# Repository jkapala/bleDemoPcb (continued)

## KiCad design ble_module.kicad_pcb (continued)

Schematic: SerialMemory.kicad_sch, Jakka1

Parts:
C24, C25, C28: 100 nF; C_0603_1608Metric
C26, C27: 22 uF; C_1206_3216Metric
D7, D8, D9: ESD321x; SODFL1608X77N; Manufacturer_Part_Number ESD321DYAR; Mouser Part Number 595-ESD321DYAR
D10: PESD3V3X4UHMYL; SON45P80X130X43-6N; Manufacturer_Part_Number PESD3V3X4UHMYL; Mouser Part Number 771-PESD3V3X4UHMYL
J3: Micro_SD_Card; GCT_MEM2061-01-188-00-A_REVA
R27, R29, R30, R32: 10k; R_0603_1608Metric
R28: 22R; R_0603_1608Metric
R31: 10k; R_0603_1608Metric; not fitted
U4: CAT24C256; SOIC-8_3.9x4.9mm_P1.27mm
U5: MX25L12833FM2I; SOP-8_5.28x5.23mm_P1.27mm

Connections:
+3V3: C24.1, C25.1, C26.1, C27.1, C28.1, D9.1 (K), J3.4 (VDD), R27.1, R29.1, R30.1, R31.2, R32.2, U4.8 (VCC), U5.8 (VCC); also elsewhere on the board
/Serial Memory/DAT1: D7.1 (K), J3.8 (DAT1), R32.1
/Serial Memory/DAT2: D8.1 (K), J3.1 (DAT2), R30.2
EEPROM_WP: U4.7 (WP); also elsewhere on the board
GND: C24.2, C25.2, C26.2, C27.2, C28.2, D7.2 (A), D8.2 (A), D9.2 (A), D10.2 (CA_1), D10.5 (CA_2), J3.6 (VSS), J3.9 (SHIELD), U4.1 (A0), U4.2 (A1), U4.3 (A2), U4.4 (GND), U5.4 (GND); also elsewhere on the board
I2C_SCL: U4.6 (SCL); also elsewhere on the board
I2C_SDA: U4.5 (SDA); also elsewhere on the board
QSPI_CLK: R28.1; also elsewhere on the board
QSPI_CLK_PIN: R28.2, U5.6 (SCLK); also elsewhere on the board
QSPI_IO0: U5.5 (SI/SIO0); also elsewhere on the board
QSPI_IO1: U5.2 (SO/SIO1); also elsewhere on the board
QSPI_IO2: U5.3 (~WP/SIO2); also elsewhere on the board
QSPI_IO3: U5.7 (~HOLD/SIO3); also elsewhere on the board
QSPI_NCS: R27.2, U5.1 (~CS); also elsewhere on the board
SPI2_MISO: D10.1 (K1), J3.7 (DAT0), R31.1; also elsewhere on the board
SPI2_MOSI: D10.4 (K3), J3.3 (CMD); also elsewhere on the board
SPI2_NSS: D10.6 (K4), J3.2 (DAT3/CD), R29.2; also elsewhere on the board
SPI2_SCK: D10.3 (K2), J3.5 (CLK); also elsewhere on the board

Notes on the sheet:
ALT: MX25L12833FZNI-10G
Micro SD
ESD protection
Addr: 1010 000
16 MB NOR Flash
32 KB EEPROM

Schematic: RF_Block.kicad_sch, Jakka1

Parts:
ANT1: AMCA72-2R470G-S1F-T4; AMCA722R470GS1FT4; Manufacturer_Part_Number AMCA72-2R470G-S1F-T4; Mouser Part Number 815-CA722R470GS1FT4
C47, C48: 0.8 pF; C_0402_1005Metric
C49: 0.3 pF; C_0402_1005Metric
J6: Conn_Coaxial; U.FL_Molex_MCRF_73412-0110_Vertical
L3: 2.7 nH; L_0402_1005Metric
L4: L; C_0402_1005Metric; not fitted
L5: 7.3 nH; L_0402_1005Metric
R46: 0R; R_0402_1005Metric; not fitted
U10: DLF162500LT-5028A1; DLF-4_1P6X0P8

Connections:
/RF Block/RF_50_OHM: C49.1, L3.2, U10.1 (IN)
/RF Block/RF_ANTENNA: C47.1, L4.2, R46.1, U10.3 (OUT)
GND: C48.2, C49.2, J6.2 (Ext), L4.1, L5.1, U10.2 (GND), U10.4 (GND); also elsewhere on the board
unnamed: ANT1.1, C47.2, L5.2
unnamed: J6.1 (In), R46.2
RF1: C48.1, L3.1; also elsewhere on the board

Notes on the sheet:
U.FL Connector
2450AT45A0100001E - Johanson, large
AMCA72-2R470G-S1F - Abracon
0402
GJM1555C1HR80WB01D
LQW15AN7N3G00D
LQG15HS2N7S02

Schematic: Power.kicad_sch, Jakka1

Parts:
B1: BAT-HLD-001; BATT_HLDR_LNX
C1, C10: 10 uF; C_0805_2012Metric
C2, C3, C4, C5: 10 nF; C_0603_1608Metric; Voltage 25V
C6, C7: 4.7 uF; C_0805_2012Metric
C8, C9: 330 pF; C_0603_1608Metric
C11, C12: 22 uF; C_1210_3225Metric
C13: 10 uF; C_1210_3225Metric
D1, D2: ESD321x; SODFL1608X77N; Manufacturer_Part_Number ESD321DYAR; Mouser Part Number 595-ESD321DYAR
D3, D4, D5, D6: LED; D_0603_1608Metric
J1: USB_C_Receptacle_USB2.0_16P; GCT_USB4105-GF-A
R1: 0.010R; C_1206_3216Metric
R2, R3: 10k; R_0603_1608Metric
R4, R5, R6, R7: R_US; R_0603_1608Metric
R8, R9, R10, R11: 100k; R_0603_1608Metric
R12, R19: 1k; R_0603_1608Metric
R13, R14, R17, R20: 5.1k; R_0603_1608Metric
R15, R18: 23.2k; R_0603_1608Metric
R16: 0; R_0603_1608Metric
S1: 4-1825059-2; SW_4-1825059-2
TP1: TestPoint; TestPoint_Pad_D1.0mm
U1: TPS25730DREFR; Mouser Part Number 595-TPS25730DREFR
U2: TVS1800DRV; WSON-6-1EP_2x2mm_P0.65mm_EP1x1.6mm

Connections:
3V_RTC: B1.3; also elsewhere on the board
+3V3: R4.1, R5.1, R6.1, R7.1, R16.2; also elsewhere on the board
/Power/ADCIN1: R8.2, S1.15, S1.16, U1.2 (ADCIN1)
/Power/ADCIN1-A: R12.1, S1.2
/Power/ADCIN1-B: R13.1, S1.1
/Power/ADCIN2: R9.2, S1.13, S1.14, U1.3 (ADCIN2)
/Power/ADCIN2-A: R14.1, S1.4
/Power/ADCIN2-B: R15.1, S1.3
/Power/ADCIN3: R10.2, S1.11, S1.12, U1.5 (ADCIN3)
/Power/ADCIN3-A: R17.1, S1.6
/Power/ADCIN3-B: R18.1, S1.5
/Power/ADCIN4: R11.2, S1.9, S1.10, U1.7 (ADCIN4)
/Power/ADCIN4-A: R19.1, S1.8
/Power/ADCIN4-B: R20.1, S1.7
/Power/DBG_ACC: D6.1 (K), U1.10 (DBG_ACC)
/Power/DRAIN: U1.15 (DRAIN_1), U1.30 (DRAIN_2), U1.40 (DRAIN_3)
/Power/PDO_MISMATCH: D4.1 (K), U1.6 (CAP_MIS)
/Power/PLUG_EVENT: D5.1 (K), U1.37 (PLUG_EVENT)
/Power/PLUG_FLIP: D3.1 (K), U1.13 (PLUG_FLIP)
/Power/USB_CC1: C9.1, J1.A5 (CC1), U1.28 (CC1)
/Power/USB_CC2: C8.1, J1.B5 (CC2), U1.29 (CC2)
/Power/VIN_3V3: C10.1, R16.1, U1.38 (VIN_3V3)
/Power/~FAULT_IN: R2.2, U1.18 (~FAULT_IN)
/Power/~SINK_EN: R3.2, U1.19 (~SINK_EN)
GND: B1.2, C1.2, C2.2, C3.2, C4.2, C5.2, C6.2, C7.2, C8.2, C9.2, C10.2, C11.2, C12.2, C13.2, D1.2 (A), D2.2 (A), J1.A1 (GND), J1.A12 (GND), J1.B1 (GND), J1.B12 (GND), J1.S1 (SHIELD), R12.2, R13.2, R14.2, R15.2, R17.2, R18.2, R19.2, R20.2, U1.11 (GND_1), U1.12 (GND_2), U1.14 (GND_3), U1.16 (GND_4), U1.17 (GND_5), U1.26 (RESERVED_1), U1.27 (RESERVED_2), U1.31 (GND_6), U1.34 (GND_7), U1.35 (GND_8), U1.36 (RESERVED_3), U1.39 (GND_9), U1.44 (GND_10), U2.1 (GND), U2.2 (GND), U2.3 (GND), U2.7 (GND); also elsewhere on the board
I2C_SCL: U1.9 (I2CT_SCL); also elsewhere on the board
I2C_SDA: U1.8 (I2CT_SDA); also elsewhere on the board
LDO_3V3: C1.1, R2.1, R3.1, R8.1, R9.1, R10.1, R11.1, U1.1 (LDO_3V3)
unnamed: D3.2 (A), R4.2
unnamed: D4.2 (A), R5.2
unnamed: D5.2 (A), R6.2
unnamed: D6.2 (A), R7.2
unnamed: C7.1, U1.4 (LDO_1V5)
USB_D+: D1.1 (K), J1.A6 (D+), J1.B6 (D+); also elsewhere on the board
USB_D-: D2.1 (K), J1.A7 (D-), J1.B7 (D-); also elsewhere on the board
VBUS_FROM_CONN1: J1.A4 (VBUS), J1.A9 (VBUS), J1.B4 (VBUS), J1.B9 (VBUS), R1.2, TP1.1, U2.4 (IN), U2.5 (IN), U2.6 (IN); also elsewhere on the board
VBUS_FROM_CONN2: C2.1, C3.1, C4.1, C5.1, C6.1, R1.1, U1.23 (VBUS_IN_1), U1.24 (VBUS_IN_2), U1.25 (VBUS_IN_3), U1.32 (VBUS_1), U1.33 (VBUS_2), U1.42 (VBUS_IN_4), U1.43 (VBUS_3); also elsewhere on the board
VBUS_MAIN: C11.1, C12.1, C13.1, U1.20 (PPHV_1), U1.21 (PPHV_2), U1.22 (PPHV_3), U1.41 (PPHV_4); also elsewhere on the board

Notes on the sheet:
USB 2.0 FS conn: USB4105-GF-A
Use TVS2200 for 27.7V clamp and 22V working range
1: Min V 2: Max V 3/4: Sink current
Jumper included to GND to enforce dead battery mode or route power from 3.3V rail
Status LEDs
RTC Battery Holder
Voltage clamped to 22.8V Limiting starting at 18V
LDO_3V3 is an output
10 uF for 3.3V LDO
VBUS ESD
ADDR: 00100 000 or 0010 001
PDO Config Block
leave SBU pins floating
Only USB 2.0 is supported for the STM32WB series.
Do not use

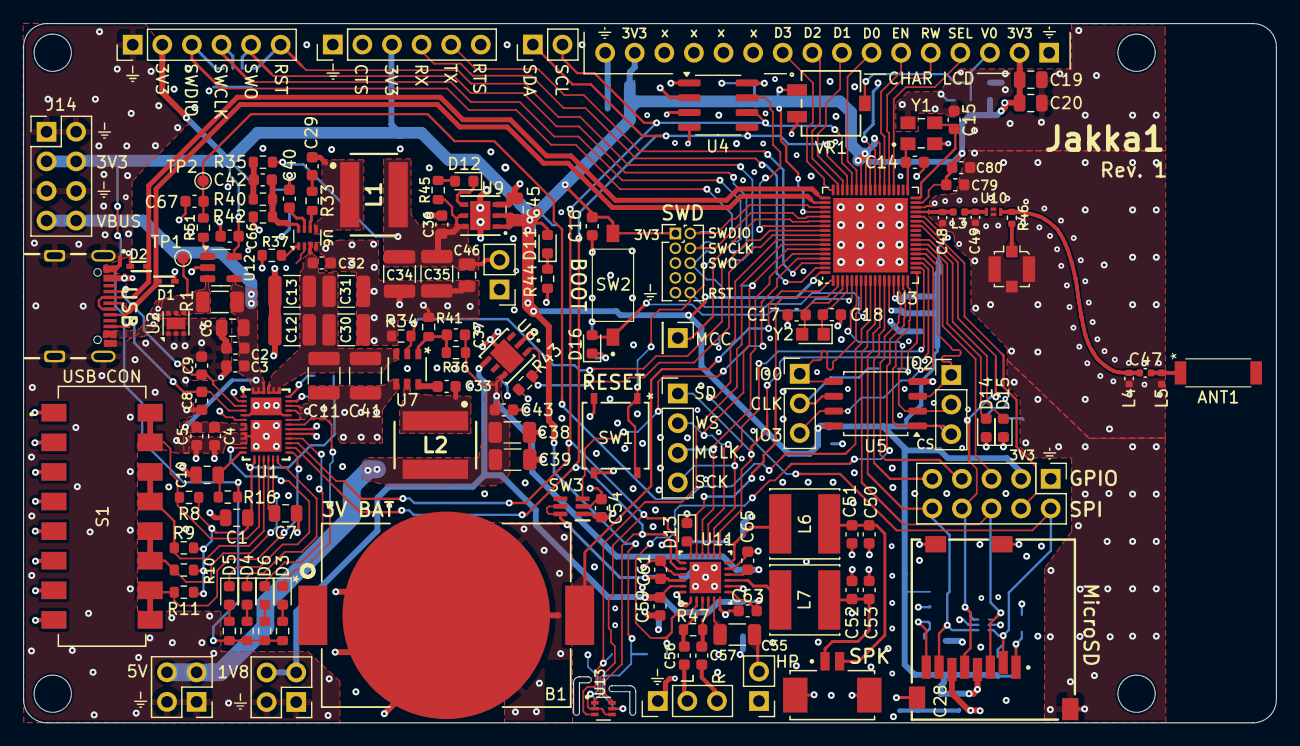
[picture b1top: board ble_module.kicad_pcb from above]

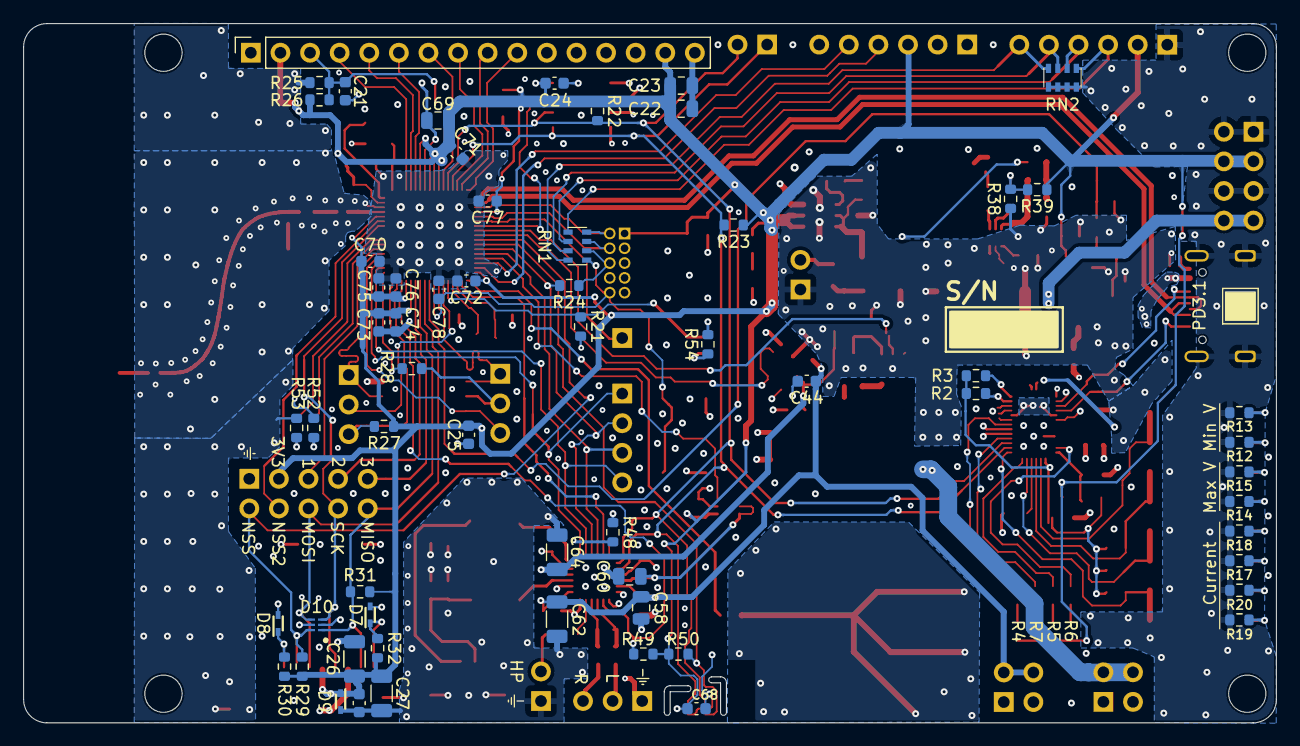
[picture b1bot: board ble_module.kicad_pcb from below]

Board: 4 copper layers, 107.5 x 60.0 mm, 207 parts (61 on the bottom side), 132 nets.

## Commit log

2024-04-18 Specifications done
2025-01-31 Design outputs in progess, schematic work started
2025-03-18 3/8/2025
2025-03-31 Layout draft complete
2025-04-08 First draft of design output, schematic, and layout complete
2025-04-08 Updated readme.md with system diagram
